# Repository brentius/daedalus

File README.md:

# daedalus
A flight computer for HPR and TVC.

Features include:

- 2 servo TVC outputs, controlled by the Teensy
- 1 servo output for parachute deploy
- 2 pyro channels for motor reignition and landing leg deployment
- Runs off a 9V battery

Components list:

- Teensy 4.1 microcontroller
- BMP180 pressure sensor
- MPU6050 IMU
- Assorted voltage regulators, etc.

Based off Teensy 4.1.
Designed in KiCad.

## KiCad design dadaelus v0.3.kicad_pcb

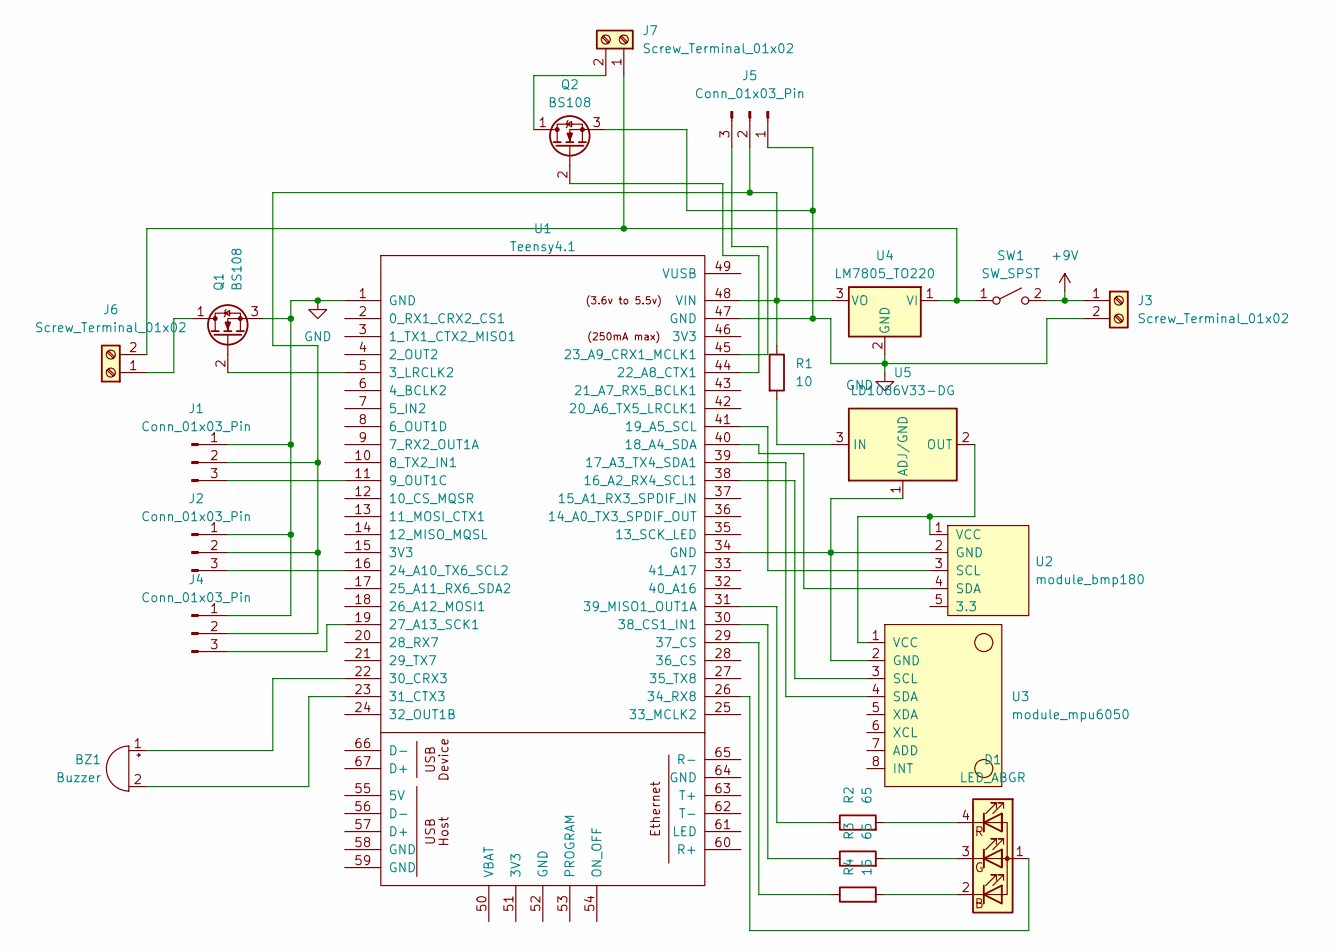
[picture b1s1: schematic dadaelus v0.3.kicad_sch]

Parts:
BZ1: Buzzer; Buzzer_TDK_PS1240P02BT_D12.2mm_H6.5mm
D1: LED_ABGR; LED_D5.0mm-4_RGB
J1, J2, J4, J5: Conn_01x03_Pin; PinHeader_1x03_P2.54mm_Vertical
J3, J6, J7: Screw_Terminal_01x02; TerminalBlock_Xinya_XY308-2.54-2P_1x02_P2.54mm_Horizontal
Q1, Q2: BS108; TO-92_Inline
R1: 10; R_Axial_DIN0204_L3.6mm_D1.6mm_P2.54mm_Vertical
R2, R3: 65; R_Axial_DIN0204_L3.6mm_D1.6mm_P2.54mm_Vertical
R4: 15; R_Axial_DIN0204_L3.6mm_D1.6mm_P2.54mm_Vertical
SW1: SW_SPST; SW_DIP_SPSTx01_Slide_9.78x4.72mm_W7.62mm_P2.54mm
U1: Teensy4.1; Teensy_4.1
U2: module_bmp180
U3: module_mpu6050
U4: LM7805_TO220; TO-220-3_Vertical
U5: LD1086V33-DG; TO-220-3_Vertical

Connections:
+9V: J3.1, SW1.2 (B)
GND: J1.1, J2.1, J3.2, J4.1, J5.1, Q1.3 (S), Q2.3 (S), U1.1 (GND), U1.47 (GND), U4.2 (GND)
unnamed: BZ1.1 (+), U1.22 (30_CRX3)
unnamed: BZ1.2 (-), U1.23 (31_CTX3)
unnamed: D1.1 (A), U1.26 (34_RX8)
unnamed: D1.2 (BK), R4.2
unnamed: D1.3 (GK), R3.2
unnamed: D1.4 (RK), R2.2
unnamed: J1.2, J2.2, J4.2, J5.2, R1.1, U1.48 (VIN), U4.3 (VO)
unnamed: J1.3, U1.11 (9_OUT1C)
unnamed: J2.3, U1.16 (24_A10_TX6_SCL2)
unnamed: J4.3, U1.19 (27_A13_SCK1)
unnamed: J5.3, U1.45 (23_A9_CRX1_MCLK1)
unnamed: J6.1, Q1.1 (D)
unnamed: J6.2, J7.1, SW1.1 (A), U4.1 (VI)
unnamed: J7.2, Q2.1 (D)
unnamed: Q1.2 (G), U1.5 (3_LRCLK2)
unnamed: Q2.2 (G), U1.44 (22_A8_CTX1)
unnamed: U1.38 (16_A2_RX4_SCL1), U3.3 (SCL)
unnamed: U1.39 (17_A3_TX4_SDA1), U3.4 (SDA)
unnamed: U1.40 (18_A4_SDA), U2.4 (SDA)
unnamed: U1.41 (19_A5_SCL), U2.3 (SCL)
unnamed: R4.1, U1.29 (37_CS)
unnamed: R3.1, U1.30 (38_CS1_IN1)
unnamed: R2.1, U1.31 (39_MISO1_OUT1A)
unnamed: U1.34 (GND), U2.2 (GND), U3.2 (GND), U5.1 (ADJ/GND)
unnamed: U2.1 (VCC), U3.1 (VCC), U5.2 (OUT)
unnamed: R1.2, U5.3 (IN)

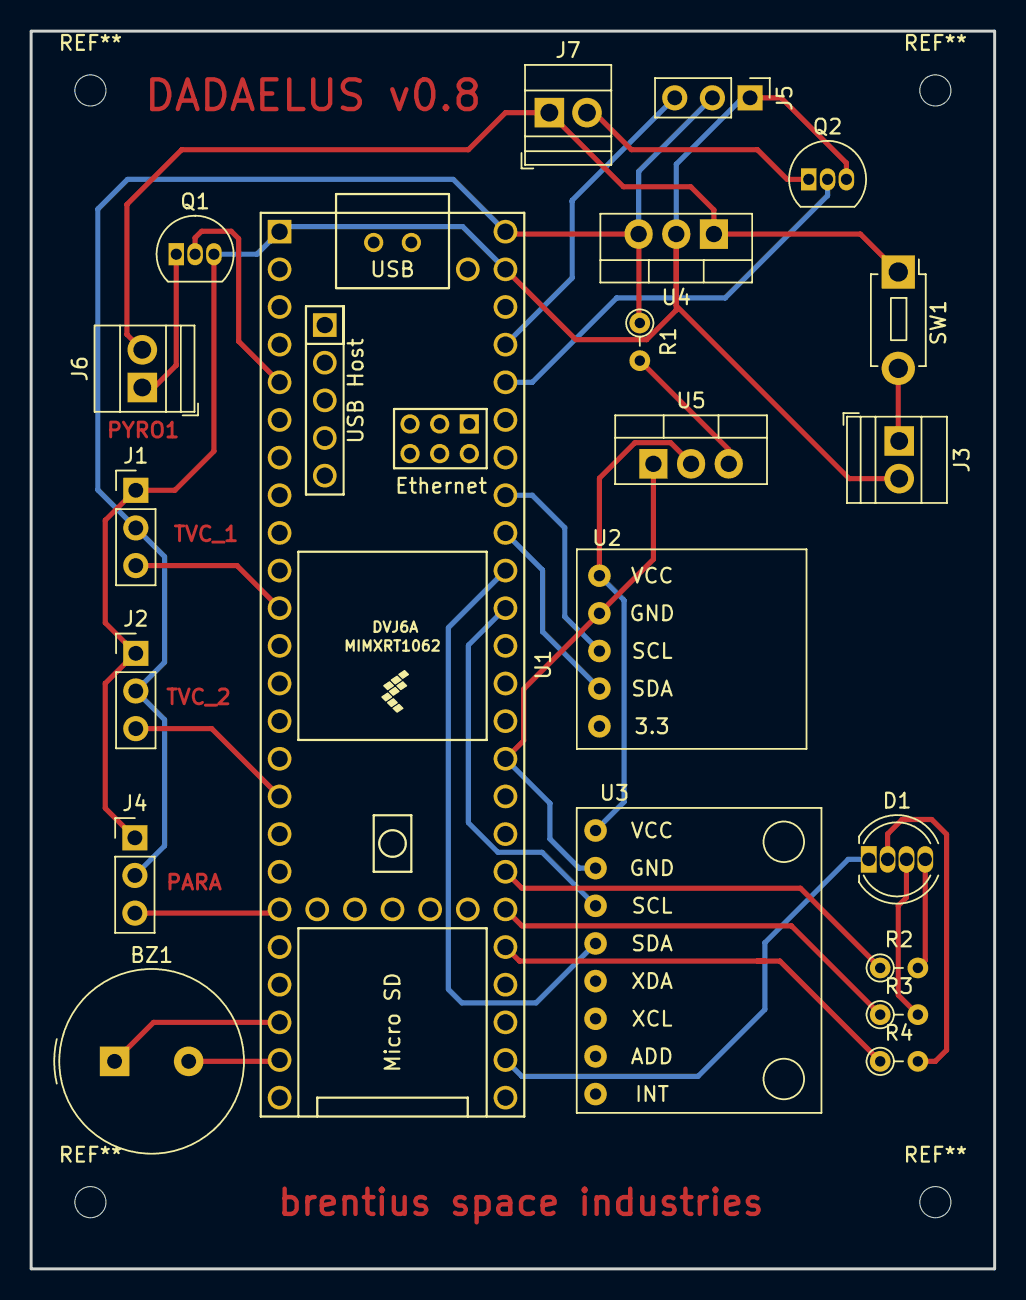
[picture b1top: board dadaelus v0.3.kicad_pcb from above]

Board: 2 copper layers, 65.0 x 83.5 mm, 21 parts (0 on the bottom side), 28 nets.

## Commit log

2024-06-20 Added files via upload
    Includes gerber files, drill files and the design files
